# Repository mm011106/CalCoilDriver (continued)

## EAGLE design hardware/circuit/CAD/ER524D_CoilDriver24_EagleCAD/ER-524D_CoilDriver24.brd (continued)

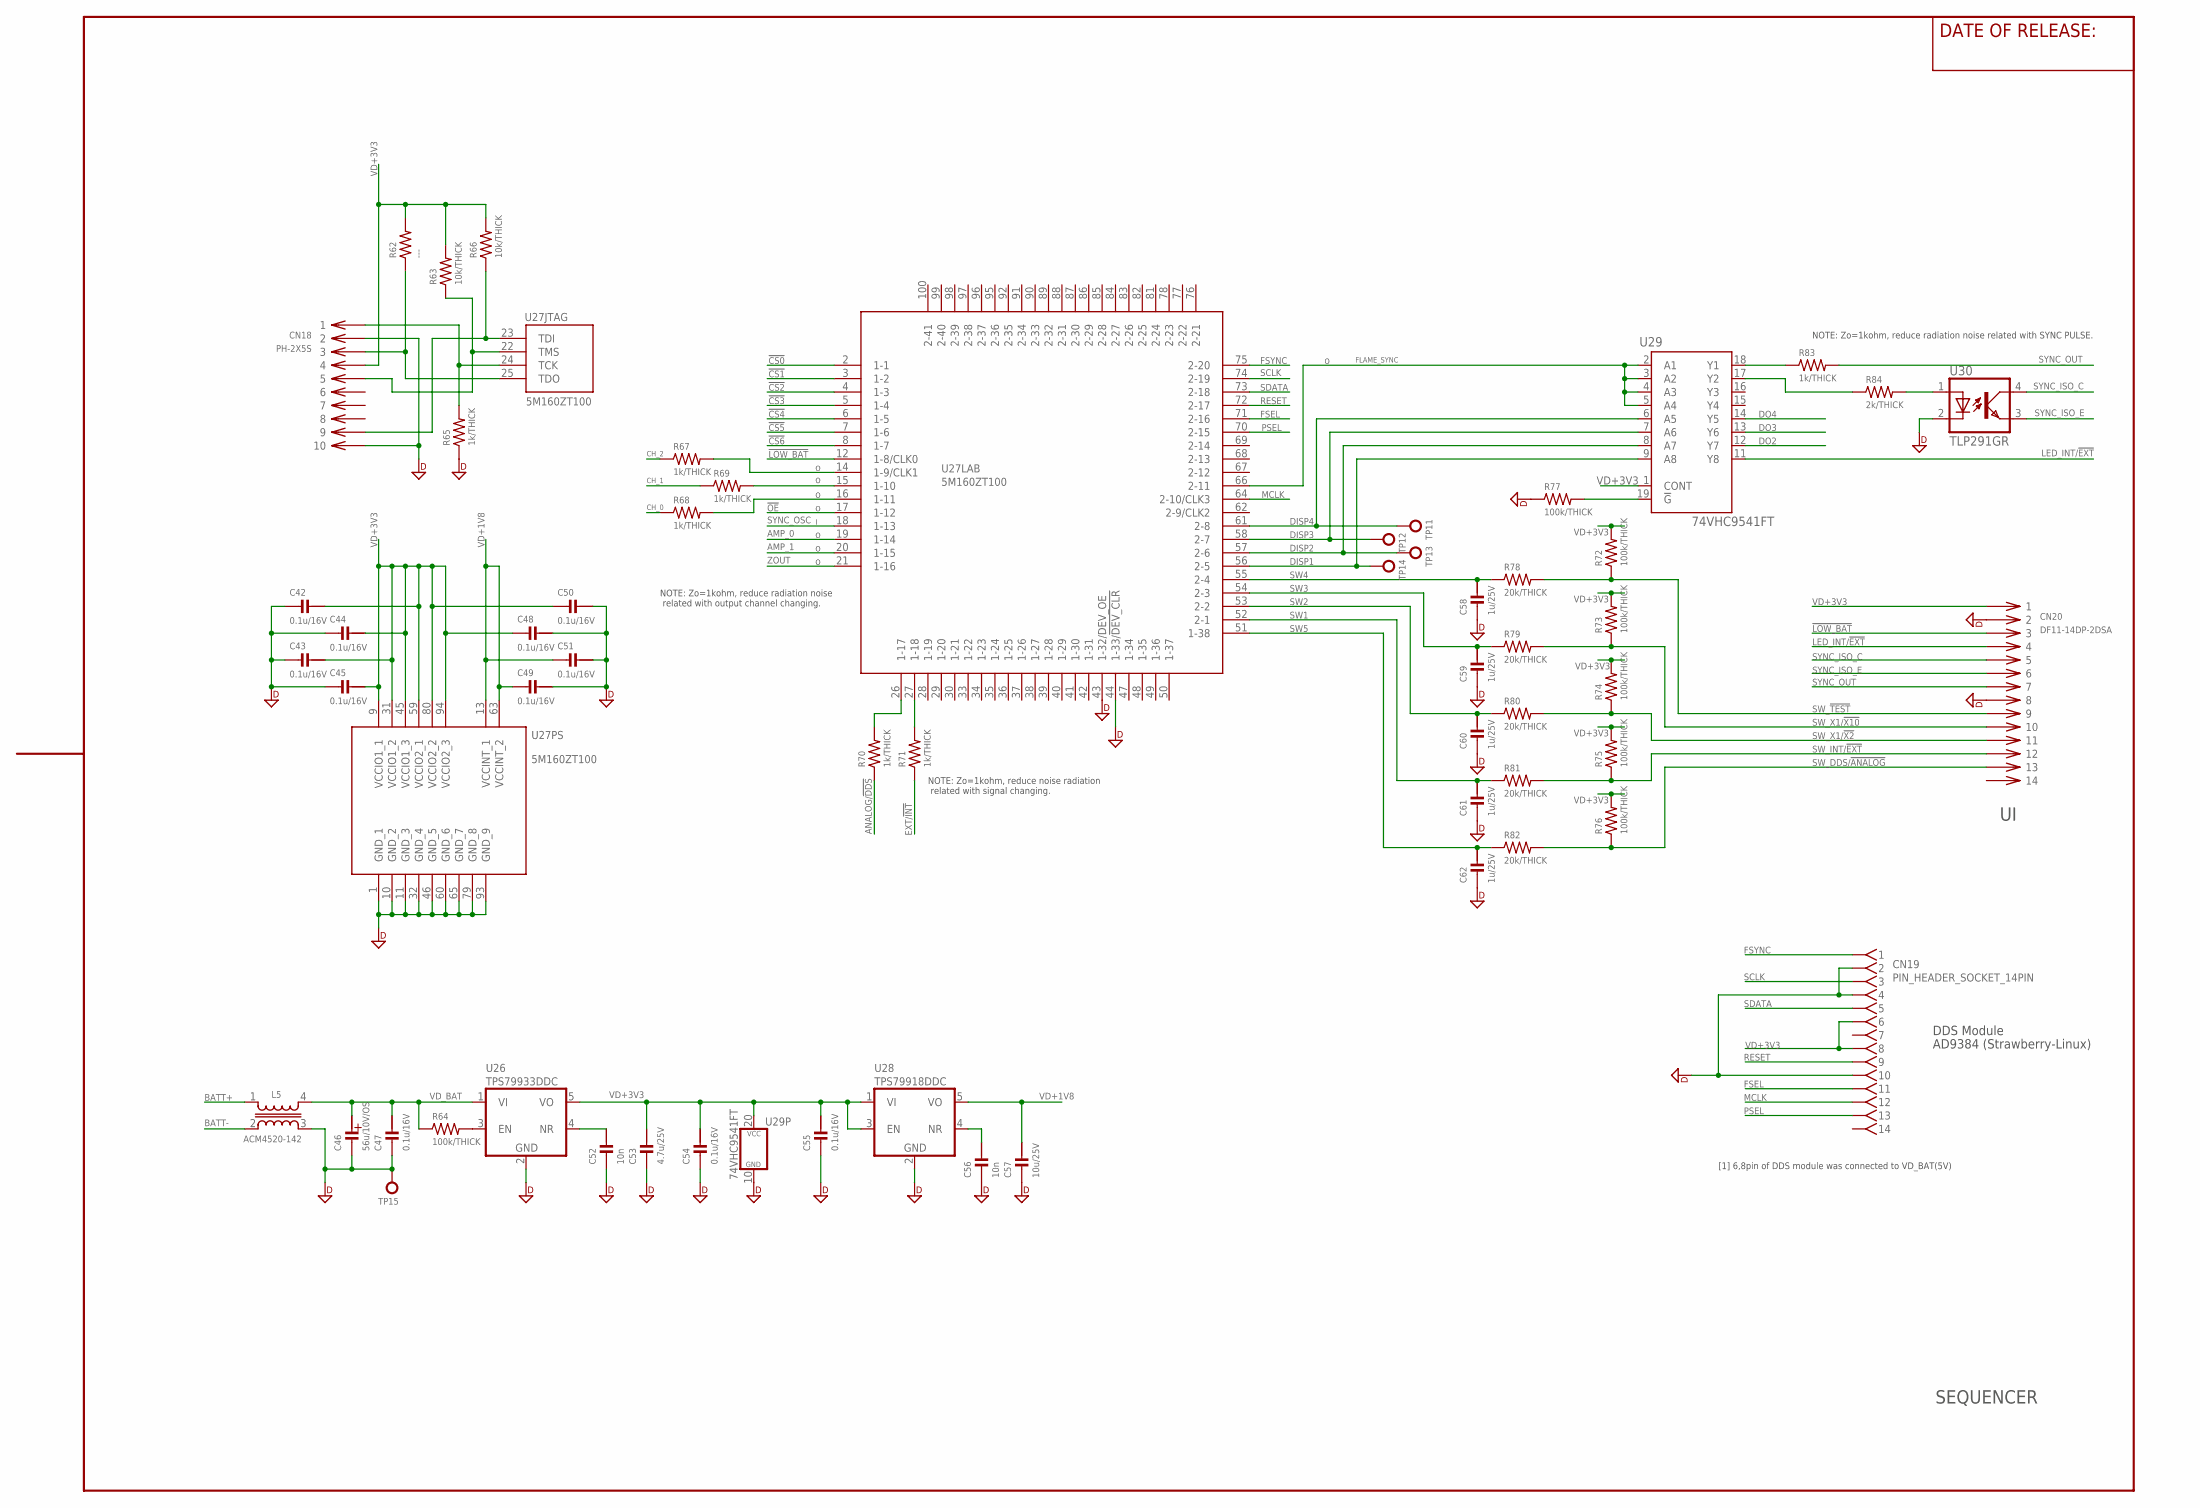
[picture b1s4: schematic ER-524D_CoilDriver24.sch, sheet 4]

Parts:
C42, C43, C44, C45, C47, C48, C49, C50, C51, C54, C55: 0.1u/16V; CM1005
C46: 56u/10V/OS; PHI_6.3
C52, C56: 10n; CM2012
C53: 4.7u/25V; CM2012
C57: 10u/25V; CM2012
C58, C59, C60, C61, C62: 1u/25V; CM1608
CN18: PH-2X5S; PIN_HEADER_10PIN
CN19: PIN_HEADER_SOCKET_14PIN
CN20: DF11-14DP-2DSA
L5: ACM4520-142; ACM4520
R62: ---; RM1608
R63, R66: 10k/THICK; RM1608
R64, R72, R73, R74, R75, R76, R77: 100k/THICK; RM1608
R65, R67, R68, R69, R70, R71, R83: 1k/THICK; RM1608
R78, R79, R80, R81, R82: 20k/THICK; RM1608
R84: 2k/THICK; RM1608
TP11, TP12, TP13, TP14: TP-1MM_PAD; TP_PAD_1MM
TP15: TP-LC3G; TP_TH_0R9MM
U26: TPS79933DDC; SOT-23-5
U27: 5M160ZT100; QFP100_0.5
U28: TPS79918DDC; SOT-23-5
U29: 74VHC9541FT; TSSOP20-P-0044-065A
U30: TLP291GR; SO4(11-3C1)(TOSHIBA)

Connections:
!CS0: U27.2 (1-1); also elsewhere on the board
!CS1: U27.3 (1-2); also elsewhere on the board
!CS2: U27.4 (1-3); also elsewhere on the board
!CS3: U27.5 (1-4); also elsewhere on the board
!CS4: U27.6 (1-5); also elsewhere on the board
!CS5: U27.7 (1-6); also elsewhere on the board
!CS6: U27.8 (1-7); also elsewhere on the board
!LOW_BAT: CN20.3, U27.12 (1-8/CLK0); also elsewhere on the board
!OE: U27.17 (1-12)
AMP_0: U27.19 (1-14); also elsewhere on the board
AMP_1: U27.20 (1-15); also elsewhere on the board
ANALOG/!DDS!: R70.1; also elsewhere on the board
BATT+: L5.1; also elsewhere on the board
BATT-: L5.2 (3); also elsewhere on the board
CH_0: R68.1; also elsewhere on the board
CH_1: R69.1; also elsewhere on the board
CH_2: R67.1; also elsewhere on the board
DGND: C42.2, C43.2, C44.2, C45.2, C46.NEG, C47.2, C48.1, C49.1, C50.1, C51.1, C52.2, C53.2, C54.2, C55.2, C56.2, C57.2, C58.2, C59.2, C60.2, C61.2, C62.2, CN18.2, CN18.10, CN19.2, CN19.4, CN19.10, CN20.2, CN20.8, L5.3 (4), R65.1, R77.1, TP15.1, U26.2 (GND), U27.1 (GND_1), U27.10 (GND_2), U27.11 (GND_3), U27.32 (GND_4), U27.43 (1-32/DEV_OE), U27.44 (1-33/!DEV_CLR), U27.46 (GND_5), U27.60 (GND_6), U27.65 (GND_7), U27.79 (GND_8), U27.93 (GND_9), U28.2 (GND), U29.10 (GND), U30.2 (C); also elsewhere on the board
DISP1: TP14.P$1, U27.56 (2-5), U29.9 (A8)
DISP2: TP13.P$1, U27.57 (2-6), U29.8 (A7)
DISP3: TP12.P$1, U27.58 (2-7), U29.7 (A6)
DISP4: TP11.P$1, U27.61 (2-8), U29.6 (A5)
DO2: U29.12 (Y7)
DO3: U29.13 (Y6)
DO4: U29.14 (Y5)
EXT/!INT!: R71.1; also elsewhere on the board
FLAME_SYNC: U27.66 (2-11), U29.2 (A1), U29.3 (A2), U29.4 (A3), U29.5 (A4)
FSEL: CN19.11, U27.71 (2-16)
FSYNC: CN19.1, U27.75 (2-20)
LED_INT/!EXT!: CN20.4, U29.11 (Y8)
MCLK: CN19.12, U27.64 (2-10/CLK3)
unnamed: R69.2, U27.15 (1-10)
unnamed: R68.2, U27.16 (1-11)
unnamed: R83.1, U29.18 (Y1)
unnamed: R77.2, U29.19 (!G)
unnamed: C52.1, U26.4 (NR)
unnamed: R64.2, U26.3 (EN)
unnamed: R70.2, U27.26 (1-17)
unnamed: CN18.9, R66.1, U27.23 (TDI)
unnamed: CN18.1, R65.2, U27.24 (TCK)
unnamed: R67.2, U27.14 (1-9/CLK1)
unnamed: R71.2, U27.27 (1-18)
unnamed: CN18.3, R62.1, U27.25 (TDO)
unnamed: CN18.5, R63.1, U27.22 (TMS)
unnamed: R84.1, U29.17 (Y2)
unnamed: C56.1, U28.4 (NR)
unnamed: R84.2, U30.1 (A)
PSEL: CN19.13, U27.70 (2-15)
RESET: CN19.9, U27.72 (2-17)
SCLK: CN19.3, U27.74 (2-19)
SDATA: CN19.5, U27.73 (2-18)
SW1: C61.1, R81.1, U27.52 (2-1)
SW2: C60.1, R80.1, U27.53 (2-2)
SW3: C59.1, R79.1, U27.54 (2-3)
SW4: C58.1, R78.1, U27.55 (2-4)
SW5: C62.1, R82.1, U27.51 (1-38)
SW_!TEST!: CN20.9, R72.1, R78.2
SW_DDS/!ANALOG!: CN20.13, R76.1, R82.2
SW_INT/!EXT: CN20.12, R75.1, R81.2
SW_X1/!X2!: CN20.11, R74.1, R80.2
SW_X1/!X10!: CN20.10, R73.1, R79.2
SYNC_ISO_C: CN20.5, U30.4 (COL)
SYNC_ISO_E: CN20.6, U30.3 (EMI)
SYNC_OSC: U27.18 (1-13); also elsewhere on the board
SYNC_OUT: CN20.7, R83.2
VD+1V8: C49.2, C51.2, C57.1, U27.13 (VCCINT_1), U27.63 (VCCINT_2), U28.5 (VO)
VD+3V3: C42.1, C43.1, C44.1, C45.1, C48.2, C50.2, C53.1, C54.1, C55.1, CN18.4, CN19.6, CN19.8, CN20.1, R62.2, R63.2, R66.2, R72.2, R73.2, R74.2, R75.2, R76.2, U26.5 (VO), U27.9 (VCCIO1_1), U27.31 (VCCIO1_2), U27.45 (VCCIO1_3), U27.59 (VCCIO2_1), U27.80 (VCCIO2_2), U27.94 (VCCIO2_3), U28.1 (VI), U28.3 (EN), U29.1 (CONT), U29.20 (VCC); also elsewhere on the board
VD_BAT: C46.POS, C47.1, L5.4 (2), R64.1, U26.1 (VI); also elsewhere on the board
ZOUT: U27.21 (1-16); also elsewhere on the board

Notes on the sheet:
SEQUENCER
DDS Module
AD9384 (Strawberry-Linux)
[1] 6,8pin of DDS module was connected to VD_BAT(5V)
NOTE: Zo=1kohm, reduce radiation noise related with SYNC PULSE.
NOTE: Zo=1kohm, reduce radiation noise related with output channel changing.
NOTE: Zo=1kohm, reduce noise radiation related with signal changing.

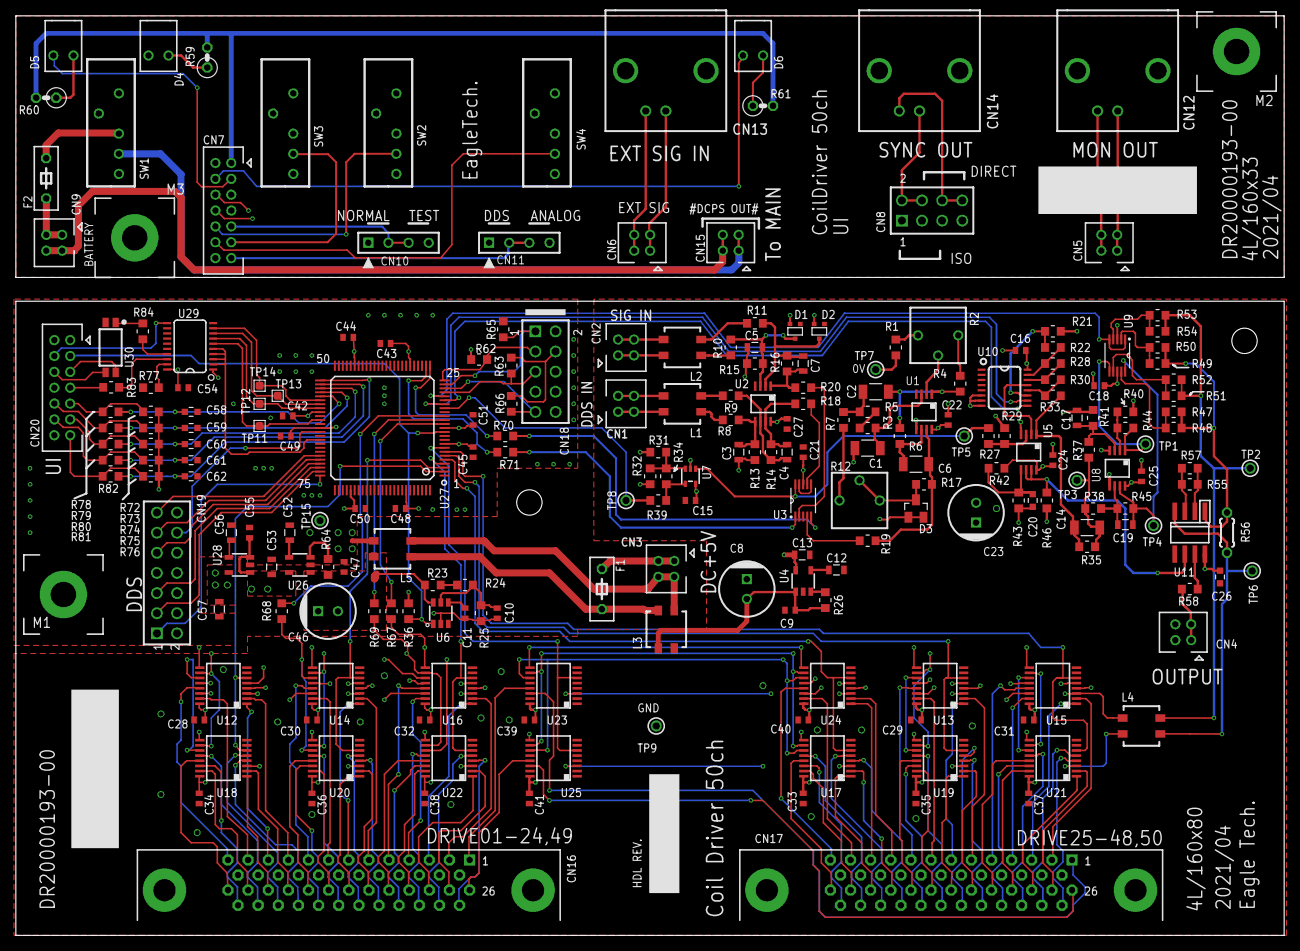
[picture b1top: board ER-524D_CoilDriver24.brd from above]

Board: 4 copper layers, 160.0 x 116.0 mm, 231 parts (0 on the bottom side), 260 nets.

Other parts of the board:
U$2: 3MM_STAT

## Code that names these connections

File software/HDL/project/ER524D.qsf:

# -------------------------------------------------------------------------- #
#
# Copyright (C) 2019  Intel Corporation. All rights reserved.
# Your use of Intel Corporation's design tools, logic functions
# and other software and tools, and any partner logic
# functions, and any output files from any of the foregoing
# (including device programming or simulation files), and any
# associated documentation or information are expressly subject
# to the terms and conditions of the Intel Program License
# Subscription Agreement, the Intel Quartus Prime License Agreement,
# the Intel FPGA IP License Agreement, or other applicable license
# agreement, including, without limitation, that your use is for
# the sole purpose of programming logic devices manufactured by
# Intel and sold by Intel or its authorized distributors.  Please
# refer to the applicable agreement for further details, at
# https://fpgasoftware.intel.com/eula.
#
# -------------------------------------------------------------------------- #
#
# Quartus Prime
# Version 19.1.0 Build 670 09/22/2019 SJ Lite Edition
# Date created = 08:14:32  May 07, 2020
#
# -------------------------------------------------------------------------- #
#
# Notes:
#
# 1) The default values for assignments are stored in the file:
#		ER524D_assignment_defaults.qdf
#    If this file doesn't exist, see file:
#		assignment_defaults.qdf
#
# 2) Altera recommends that you do not modify this file. This
#    file is updated automatically by the Quartus Prime software
#    and any changes you make may be lost or overwritten.
#
# -------------------------------------------------------------------------- #


set_global_assignment -name FAMILY "MAX V"
set_global_assignment -name DEVICE 5M160ZT100I5
set_global_assignment -name TOP_LEVEL_ENTITY PhantomDriver
set_global_assignment -name ORIGINAL_QUARTUS_VERSION 23.1STD.1
set_global_assignment -name PROJECT_CREATION_TIME_DATE "15:24:31  SEPTEMBER 05, 2025"
set_global_assignment -name LAST_QUARTUS_VERSION "23.1std.1 Lite Edition"
set_global_assignment -name PROJECT_OUTPUT_DIRECTORY output_files
set_global_assignment -name MIN_CORE_JUNCTION_TEMP "-40"
set_global_assignment -name MAX_CORE_JUNCTION_TEMP 125
set_global_assignment -name DEVICE_FILTER_PACKAGE TQFP
set_global_assignment -name DEVICE_FILTER_PIN_COUNT 100
set_global_assignment -name DEVICE_FILTER_SPEED_GRADE 5
set_global_assignment -name ERROR_CHECK_FREQUENCY_DIVISOR "-1"
set_global_assignment -name EDA_SIMULATION_TOOL "Questa Intel FPGA (VHDL)"
set_global_assignment -name EDA_TIME_SCALE "1 ps" -section_id eda_simulation
set_global_assignment -name EDA_OUTPUT_DATA_FORMAT VHDL -section_id eda_simulation
set_global_assignment -name EDA_GENERATE_FUNCTIONAL_NETLIST OFF -section_id eda_board_design_timing
set_global_assignment -name EDA_GENERATE_FUNCTIONAL_NETLIST OFF -section_id eda_board_design_symbol
set_global_assignment -name EDA_GENERATE_FUNCTIONAL_NETLIST OFF -section_id eda_board_design_signal_integrity
set_global_assignment -name EDA_GENERATE_FUNCTIONAL_NETLIST OFF -section_id eda_board_design_boundary_scan
set_global_assignment -name POWER_PRESET_COOLING_SOLUTION "NO HEAT SINK WITH STILL AIR"
set_location_assignment PIN_20 -to AMP[1]
set_location_assignment PIN_19 -to AMP[0]
set_location_assignment PIN_14 -to CH[2]
set_location_assignment PIN_15 -to CH[1]
set_location_assignment PIN_16 -to CH[0]
set_location_assignment PIN_18 -to CLK
set_location_assignment PIN_8 -to CS[6]
set_location_assignment PIN_7 -to CS[5]
set_location_assignment PIN_6 -to CS[4]
set_location_assignment PIN_5 -to CS[3]
set_location_assignment PIN_4 -to CS[2]
set_location_assignment PIN_3 -to CS[1]
set_location_assignment PIN_2 -to CS[0]
set_location_assignment PIN_61 -to D[4]
set_location_assignment PIN_58 -to D[3]
set_location_assignment PIN_57 -to D[2]
set_location_assignment PIN_56 -to D[1]
set_location_assignment PIN_71 -to FSEL
set_location_assignment PIN_75 -to FSYNC
set_location_assignment PIN_64 -to MCLK
set_location_assignment PIN_70 -to PSEL
set_location_assignment PIN_72 -to RESET
set_location_assignment PIN_74 -to SCLK
set_location_assignment PIN_73 -to SDATA
set_location_assignment PIN_55 -to SW[4]
set_location_assignment PIN_54 -to SW[3]
set_location_assignment PIN_53 -to SW[2]
set_location_assignment PIN_52 -to SW[1]
set_location_assignment PIN_66 -to SYNC
set_location_assignment PIN_21 -to ZOUT
set_location_assignment PIN_17 -to OE
set_instance_assignment -name IO_STANDARD "3.3V SCHMITT TRIGGER INPUT" -to LOW_BAT
set_location_assignment PIN_12 -to LOW_BAT
set_location_assignment PIN_51 -to SW[5]
set_location_assignment PIN_26 -to SEL_ANALOG
set_location_assignment PIN_27 -to SEL_EXT
set_global_assignment -name VHDL_FILE SEQUENCER.vhdl
set_global_assignment -name VHDL_FILE PhantomDriver_tb.vhdl
set_global_assignment -name VHDL_FILE PhantomDriver.vhdl
set_global_assignment -name VHDL_FILE OUTPUT_PATCH.vhdl
set_global_assignment -name VHDL_FILE DDS_INIT.vhdl
set_global_assignment -name VHDL_FILE counter_increment.vhdl
set_global_assignment -name VHDL_FILE counter_decrement.vhdl
set_instance_assignment -name IO_STANDARD "3.3V SCHMITT TRIGGER INPUT" -to SW[5]
set_instance_assignment -name IO_STANDARD "3.3V SCHMITT TRIGGER INPUT" -to SW[4]
set_instance_assignment -name IO_STANDARD "3.3V SCHMITT TRIGGER INPUT" -to SW[3]
set_instance_assignment -name IO_STANDARD "3.3V SCHMITT TRIGGER INPUT" -to SW[2]
set_instance_assignment -name IO_STANDARD "3.3V SCHMITT TRIGGER INPUT" -to SW[1]
set_instance_assignment -name IO_STANDARD "3.3V SCHMITT TRIGGER INPUT" -to SW
set_instance_assignment -name IO_STANDARD "3.3-V LVTTL" -to SYNC
set_global_assignment -name MIF_FILE patch_table.mif

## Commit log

2025-05-29 README.md修正中
2025-06-04 Add files
2025-06-10 update circuit/design_note
2025-06-12 add figures
2025-07-11 update design_note and files
2025-07-23 add photo(DDS)
2025-07-28 値づけ手順の追加
2025-08-06 値づけ手順 追記
2025-09-05 CalCoilDriver_Cal_block.drawio を追加しました。
2025-09-05 CalCoilDriver_Cal_block.drawio を更新します
2025-09-05 CalCoilDriver_Cal_block.png を追加しました。
2025-09-05 update /README & /calibration
2025-09-05 Add HDL files
2025-09-05 update HDL/description
2025-09-24 HDL_DDS_INIT.drawio を追加しました。
2025-09-24 HDL_DDS_INIT.drawio を更新します
2025-09-24 HDL_DDS_INIT.drawio.png を追加しました。
2025-09-25 ER524D_HDL_TopLevel_BlockDiagram.drawio を追加しました。
2025-09-25 ER524D_HDL_TopLevel_BlockDiagram.drawio を更新します
2025-09-25 ER524D_HDL_TopLevel_BlockDiagram.drawio.png を追加しました。
2025-09-26 update HDL-design_note
2025-10-08 update HDL-design_note and READMEs
2025-10-08 update /README
